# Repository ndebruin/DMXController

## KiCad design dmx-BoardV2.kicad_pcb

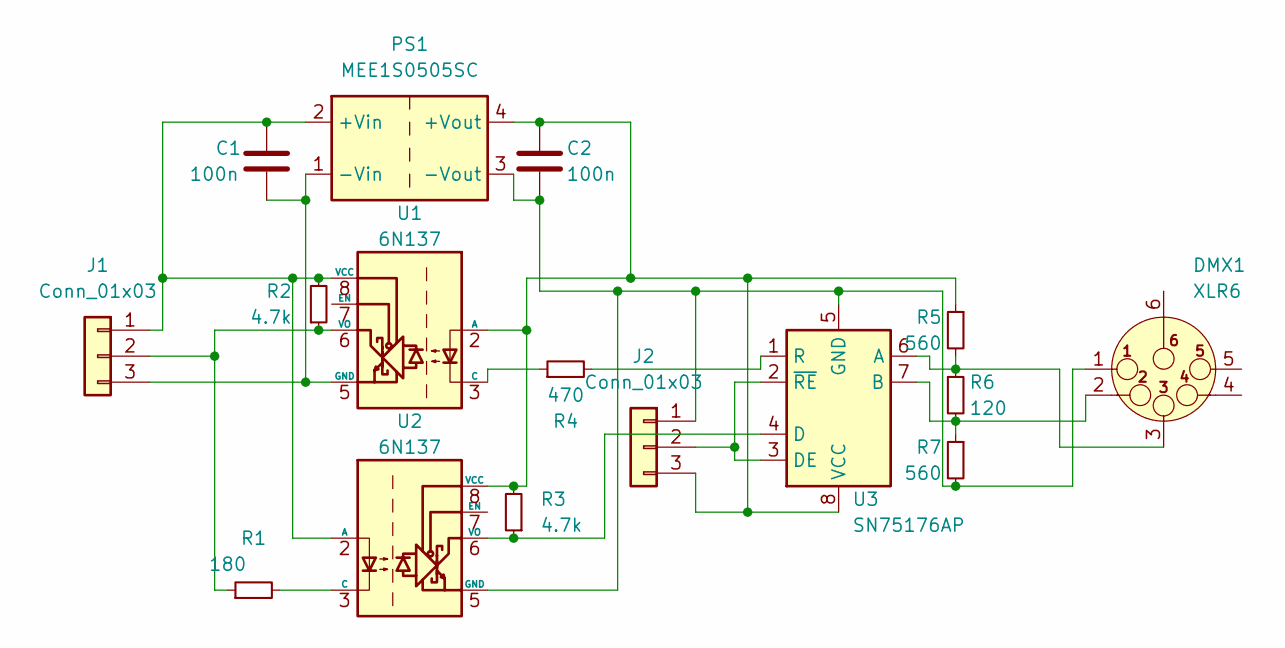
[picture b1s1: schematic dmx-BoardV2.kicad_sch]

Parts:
C1, C2: 100n; C_Disc_D3.8mm_W2.6mm_P2.50mm
DMX1: XLR6; Jack_XLR_Neutrik_NC5FAH_Horizontal
J1, J2: Conn_01x03; PinHeader_1x03_P2.54mm_Vertical
PS1: MEE1S0505SC; Converter_DCDC_Murata_MEE1SxxxxSC_THT
R1: 180; R_0805_2012Metric_Pad1.20x1.40mm_HandSolder
R2, R3: 4.7k; R_0805_2012Metric_Pad1.20x1.40mm_HandSolder
R4: 470; R_0805_2012Metric_Pad1.20x1.40mm_HandSolder
R5, R7: 560; R_0805_2012Metric_Pad1.20x1.40mm_HandSolder
R6: 120; R_0805_2012Metric_Pad1.20x1.40mm_HandSolder
U1, U2: 6N137; DIP-8_W7.62mm
U3: SN75176AP; DIP-8_W7.62mm

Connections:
unnamed: C1.1, J1.1, PS1.2 (+Vin), R2.2, U1.8 (VCC), U2.2 (A)
unnamed: C1.2, J1.3, PS1.1 (-Vin), U1.5 (GND)
unnamed: C2.1, J2.3, PS1.4 (+Vout), R3.2, R5.1, U1.2 (A), U2.8 (VCC), U3.8 (VCC)
unnamed: C2.2, DMX1.1, J2.1, PS1.3 (-Vout), R7.2, U2.5 (GND), U3.5 (GND)
unnamed: DMX1.2, R6.2, R7.1, U3.7 (B)
unnamed: DMX1.3, R5.2, R6.1, U3.6 (A)
unnamed: J1.2, R1.1, R2.1, U1.6 (VO)
unnamed: J2.2, U3.2 (~RE), U3.3 (DE)
unnamed: R1.2, U2.3 (C)
unnamed: R3.1, U2.6 (VO), U3.4 (D)
unnamed: R4.1, U1.3 (C)
unnamed: R4.2, U3.1 (R)

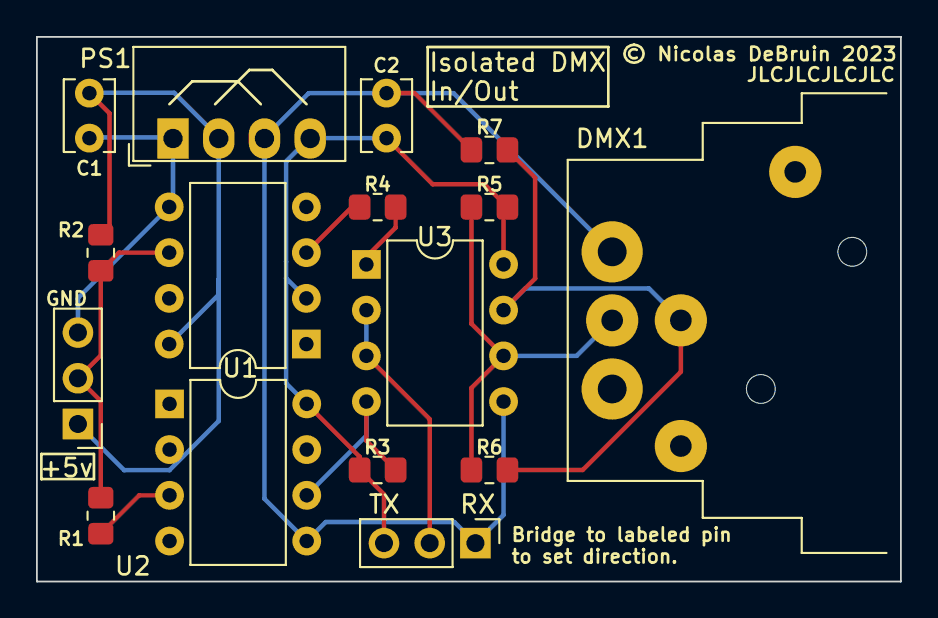
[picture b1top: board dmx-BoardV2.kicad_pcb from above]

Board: 2 copper layers, 48.0 x 30.3 mm, 16 parts (0 on the bottom side), 12 nets.

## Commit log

2024-03-18 Add KiCAD Files
2024-03-18 Add Firmware files

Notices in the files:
dmx-BoardV2.kicad_pcb:
© Nicolas DeBruin 2023
